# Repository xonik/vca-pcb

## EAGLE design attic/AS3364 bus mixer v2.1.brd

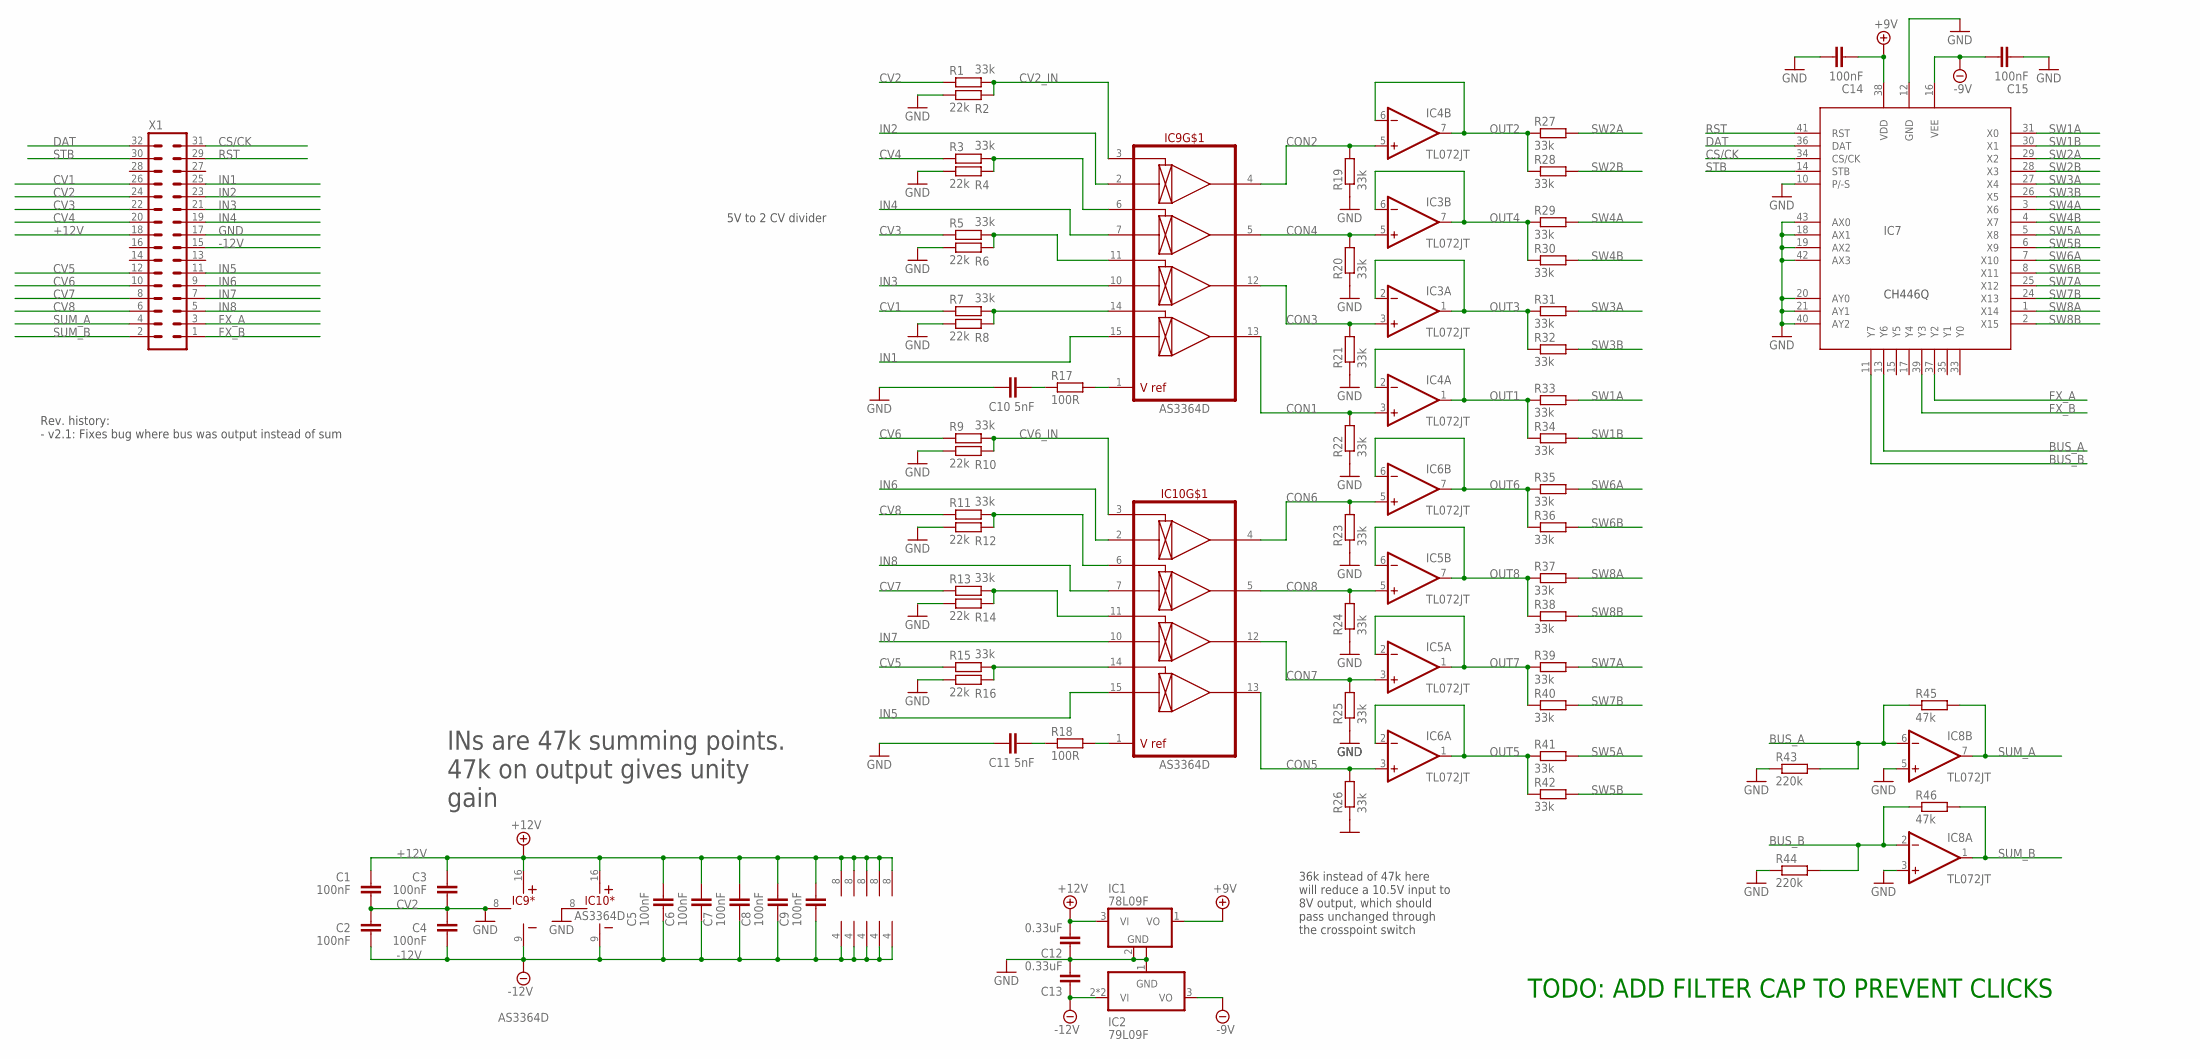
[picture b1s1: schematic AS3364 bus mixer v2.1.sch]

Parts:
C1, C2, C3, C4, C5, C6, C7, C8, C9, C14, C15: 100nF; C0402
C10, C11: 5nF; C0402
C12, C13: 0.33uF; C0603
IC1: 78L09F; SOT89
IC2: 79L09F; SOT89
IC3, IC4, IC5, IC6, IC8: TL072JT; TSSOP8J
IC7: CH446Q; LQFP-44-J
IC9, IC10: AS3364D; DIL16J
R1, R3, R5, R7, R9, R11, R13, R15, R19, R20, R21, R22, R23, R24, R25, R26, R27, R28, R29, R30, R31, R32, R33, R34, R35, R36, R37, R38, R39, R40, R41, R42: 33k; R0402
R2, R4, R6, R8, R10, R12, R14, R16: 22k; R0402
R17, R18: 100R; R0402
R43, R44: 220k; R0402
R45, R46: 47k; R0402
X1: MA16-2WJ

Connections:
+9V: C14.1, IC1.1 (VO), IC7.38 (VDD)
+12V: C1.2, C3.2, C5.2, C6.2, C7.2, C8.2, C9.2, C12.2, IC1.3 (VI), IC3.8 (V+), IC4.8 (V+), IC5.8 (V+), IC6.8 (V+), IC8.8 (V+), IC9.16 (V+), IC10.16 (V+), X1.18
-9V: C15.2, IC2.3 (VO), IC7.16 (VEE)
-12V: C2.1, C4.1, C5.1, C6.1, C7.1, C8.1, C9.1, C13.1, IC2.2 (VI), IC2.2@1 (VI), IC3.4 (V-), IC4.4 (V-), IC5.4 (V-), IC6.4 (V-), IC8.4 (V-), IC9.9 (V-), IC10.9 (V-), X1.15
BUS_A: IC7.13 (Y6), IC8.6 (-IN), R43.2, R45.1
BUS_B: IC7.11 (Y7), IC8.2 (-IN), R44.2, R46.1
CON1: IC4.3 (+IN), IC9.13 (OUT4), R22.2
CON2: IC4.5 (+IN), IC9.4 (OUT1), R19.2
CON3: IC3.3 (+IN), IC9.12 (OUT3), R21.2
CON4: IC3.5 (+IN), IC9.5 (OUT2), R20.2
CON5: IC6.3 (+IN), IC10.13 (OUT4), R26.2
CON6: IC6.5 (+IN), IC10.4 (OUT1), R23.2
CON7: IC5.3 (+IN), IC10.12 (OUT3), R25.2
CON8: IC5.5 (+IN), IC10.5 (OUT2), R24.2
CS/CK: IC7.34 (CS/CK), X1.31
CV1: R7.1, X1.26
CV2: R1.1, X1.24
CV2_IN: IC9.3 (CV1), R1.2, R2.2
CV3: R5.1, X1.22
CV4: R3.1, X1.20
CV5: R15.1, X1.12
CV6: R9.1, X1.10
CV6_IN: IC10.3 (CV1), R9.2, R10.2
CV7: R13.1, X1.8
CV8: R11.1, X1.6
DAT: IC7.36 (DAT), X1.32
FX_A: IC7.37 (Y2), X1.3
FX_B: IC7.39 (Y3), X1.1
GND: C1.1, C2.2, C3.1, C4.2, C10.1, C11.1, C12.1, C13.2, C14.2, C15.1, IC1.2 (GND), IC1.2@1 (GND), IC2.1 (GND), IC7.10 (P/-S), IC7.12 (GND), IC7.18 (AX1), IC7.19 (AX2), IC7.20 (AY0), IC7.21 (AY1), IC7.40 (AY2), IC7.42 (AX3), IC7.43 (AX0), IC8.3 (+IN), IC8.5 (+IN), IC9.8 (GND), IC10.8 (GND), R2.1, R4.1, R6.1, R8.1, R10.1, R12.1, R14.1, R16.1, R19.1, R20.1, R21.1, R22.1, R23.1, R24.1, R25.1, R26.1, R43.1, R44.1, X1.17
IN1: IC9.15 (IN4), X1.25
IN2: IC9.2 (IN1), X1.23
IN3: IC9.10 (IN3), X1.21
IN4: IC9.7 (IN2), X1.19
IN5: IC10.15 (IN4), X1.11
IN6: IC10.2 (IN1), X1.9
IN7: IC10.10 (IN3), X1.7
IN8: IC10.7 (IN2), X1.5
unnamed: IC10.1 (VREF), R18.2
unnamed: IC9.1 (VREF), R17.2
unnamed: IC10.6 (CV2), R11.2, R12.2
unnamed: IC10.11 (CV3), R13.2, R14.2
unnamed: IC10.14 (CV4), R15.2, R16.2
unnamed: C11.2, R18.1
unnamed: IC9.6 (CV2), R3.2, R4.2
unnamed: IC9.11 (CV3), R5.2, R6.2
unnamed: C10.2, R17.1
unnamed: IC9.14 (CV4), R7.2, R8.2
OUT1: IC4.1 (OUT), IC4.2 (-IN), R33.1, R34.1
OUT2: IC4.6 (-IN), IC4.7 (OUT), R27.1, R28.1
OUT3: IC3.1 (OUT), IC3.2 (-IN), R31.1, R32.1
OUT4: IC3.6 (-IN), IC3.7 (OUT), R29.1, R30.1
OUT5: IC6.1 (OUT), IC6.2 (-IN), R41.1, R42.1
OUT6: IC6.6 (-IN), IC6.7 (OUT), R35.1, R36.1
OUT7: IC5.1 (OUT), IC5.2 (-IN), R39.1, R40.1
OUT8: IC5.6 (-IN), IC5.7 (OUT), R37.1, R38.1
RST: IC7.41 (RST), X1.29
STB: IC7.14 (STB), X1.30
SUM_A: IC8.7 (OUT), R45.2, X1.4
SUM_B: IC8.1 (OUT), R46.2, X1.2
SW1A: IC7.31 (X0), R33.2
SW1B: IC7.30 (X1), R34.2
SW2A: IC7.29 (X2), R27.2
SW2B: IC7.28 (X3), R28.2
SW3A: IC7.27 (X4), R31.2
SW3B: IC7.26 (X5), R32.2
SW4A: IC7.3 (X6), R29.2
SW4B: IC7.4 (X7), R30.2
SW5A: IC7.5 (X8), R41.2
SW5B: IC7.6 (X9), R42.2
SW6A: IC7.7 (X10), R35.2
SW6B: IC7.8 (X11), R36.2
SW7A: IC7.25 (X12), R39.2
SW7B: IC7.24 (X13), R40.2
SW8A: IC7.1 (X14), R37.2
SW8B: IC7.2 (X15), R38.2

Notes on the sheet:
INs are 47k summing points. 47k on output gives unity gain
5V to 2 CV divider
36k instead of 47k here will reduce a 10.5V input to 8V output, which should pass unchanged through the crosspoint switch
Rev. history: - v2.1: Fixes bug where bus was output instead of sum
TODO: ADD FILTER CAP TO PREVENT CLICKS

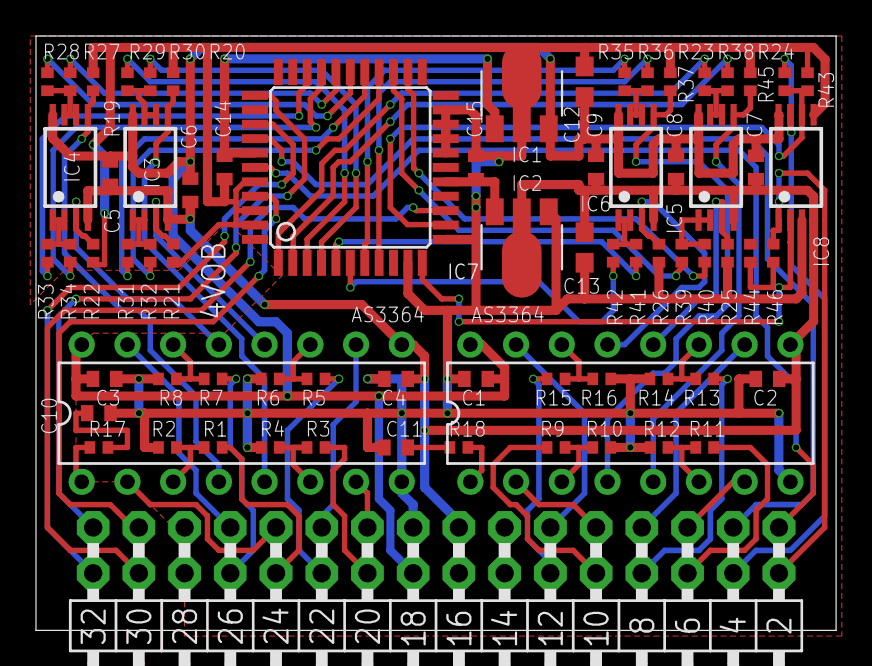
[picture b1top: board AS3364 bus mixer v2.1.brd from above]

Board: 2 copper layers, 44.5 x 33.0 mm, 73 parts (1 on the bottom side), 75 nets.

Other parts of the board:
U$1: XONIK_LOGO_28

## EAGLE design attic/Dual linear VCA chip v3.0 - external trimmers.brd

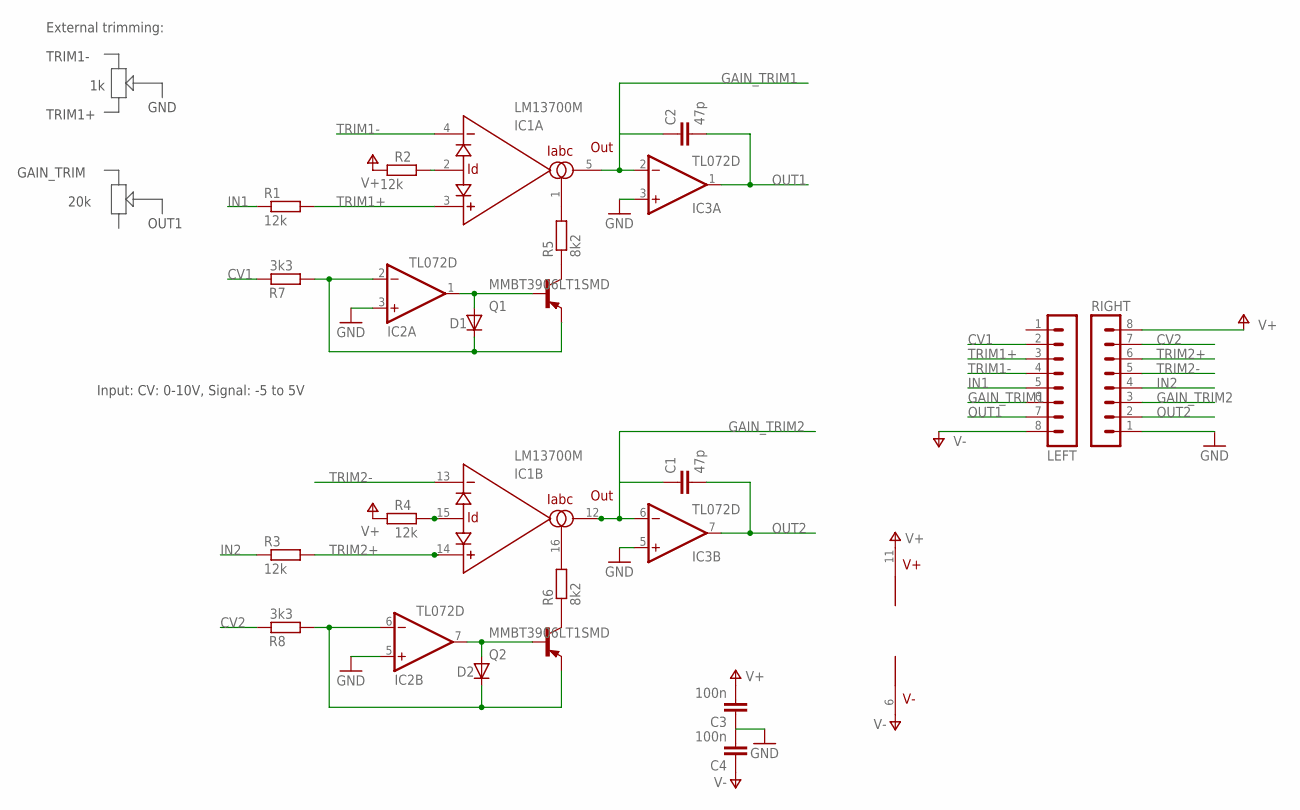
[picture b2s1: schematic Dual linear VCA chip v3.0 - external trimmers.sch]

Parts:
C1, C2: 47p; C0805
C3, C4: 100n; C0805
D1, D2: DIODE-SOD80C; SOD80C
IC1: LM13700M; SO16
IC2, IC3: TL072D; SO08
LEFT: MA08-1JC; MA08-1J
Q1, Q2: MMBT3906LT1SMD; SOT23-BEC
R1, R2, R3, R4: 12k; R0805
R5, R6: 8k2; R0805
R7, R8: 3k3; R0805
RIGHT: MA08-1JC; MA08-1J

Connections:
CV1: LEFT.2, R7.2
CV2: R8.2, RIGHT.7
GAIN_TRIM1: C2.1, IC1.5 (OUT), IC3.2 (-IN), LEFT.6
GAIN_TRIM2: C1.1, IC1.12 (OUT), IC3.6 (-IN), RIGHT.3
GND: C3.1, C4.2, IC2.3 (+IN), IC2.5 (+IN), IC3.3 (+IN), IC3.5 (+IN), RIGHT.1
IN1: LEFT.5, R1.1
IN2: R3.1, RIGHT.4
unnamed: Q1.C, R5.1
unnamed: Q2.C, R6.1
unnamed: D1.C, IC2.2 (-IN), Q1.E, R7.1
unnamed: IC1.1 (IABC), R5.2
unnamed: IC1.2 (ID), R2.2
unnamed: D2.A, IC2.7 (OUT), Q2.B
unnamed: D1.A, IC2.1 (OUT), Q1.B
unnamed: D2.C, IC2.6 (-IN), Q2.E, R8.1
unnamed: IC1.16 (IABC), R6.2
unnamed: IC1.15 (ID), R4.2
OUT1: C2.2, IC3.1 (OUT), LEFT.7
OUT2: C1.2, IC3.7 (OUT), RIGHT.2
TRIM1+: IC1.3 (+IN), LEFT.3, R1.2
TRIM1-: IC1.4 (-IN), LEFT.4
TRIM2+: IC1.14 (+IN), R3.2, RIGHT.6
TRIM2-: IC1.13 (-IN), RIGHT.5
V+: C3.2, IC1.11 (V+), IC2.8 (V+), IC3.8 (V+), R2.1, R4.1, RIGHT.8
V-: C4.1, IC1.6 (V-), IC2.4 (V-), IC3.4 (V-), LEFT.8

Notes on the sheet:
Input: CV: 0-10V, Signal: -5 to 5V
TRIM1-
TRIM1+
GND
External trimming:
GAIN_TRIM
OUT1
20k

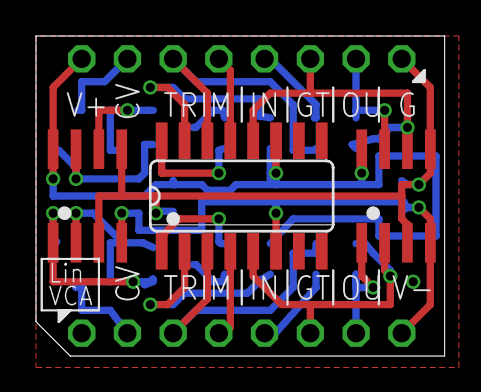
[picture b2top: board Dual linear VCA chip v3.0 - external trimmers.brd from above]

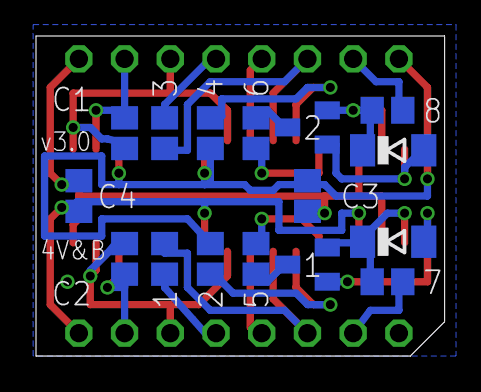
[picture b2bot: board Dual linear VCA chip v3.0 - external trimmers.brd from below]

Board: 2 copper layers, 22.7 x 17.8 mm, 21 parts (16 on the bottom side), 25 nets.

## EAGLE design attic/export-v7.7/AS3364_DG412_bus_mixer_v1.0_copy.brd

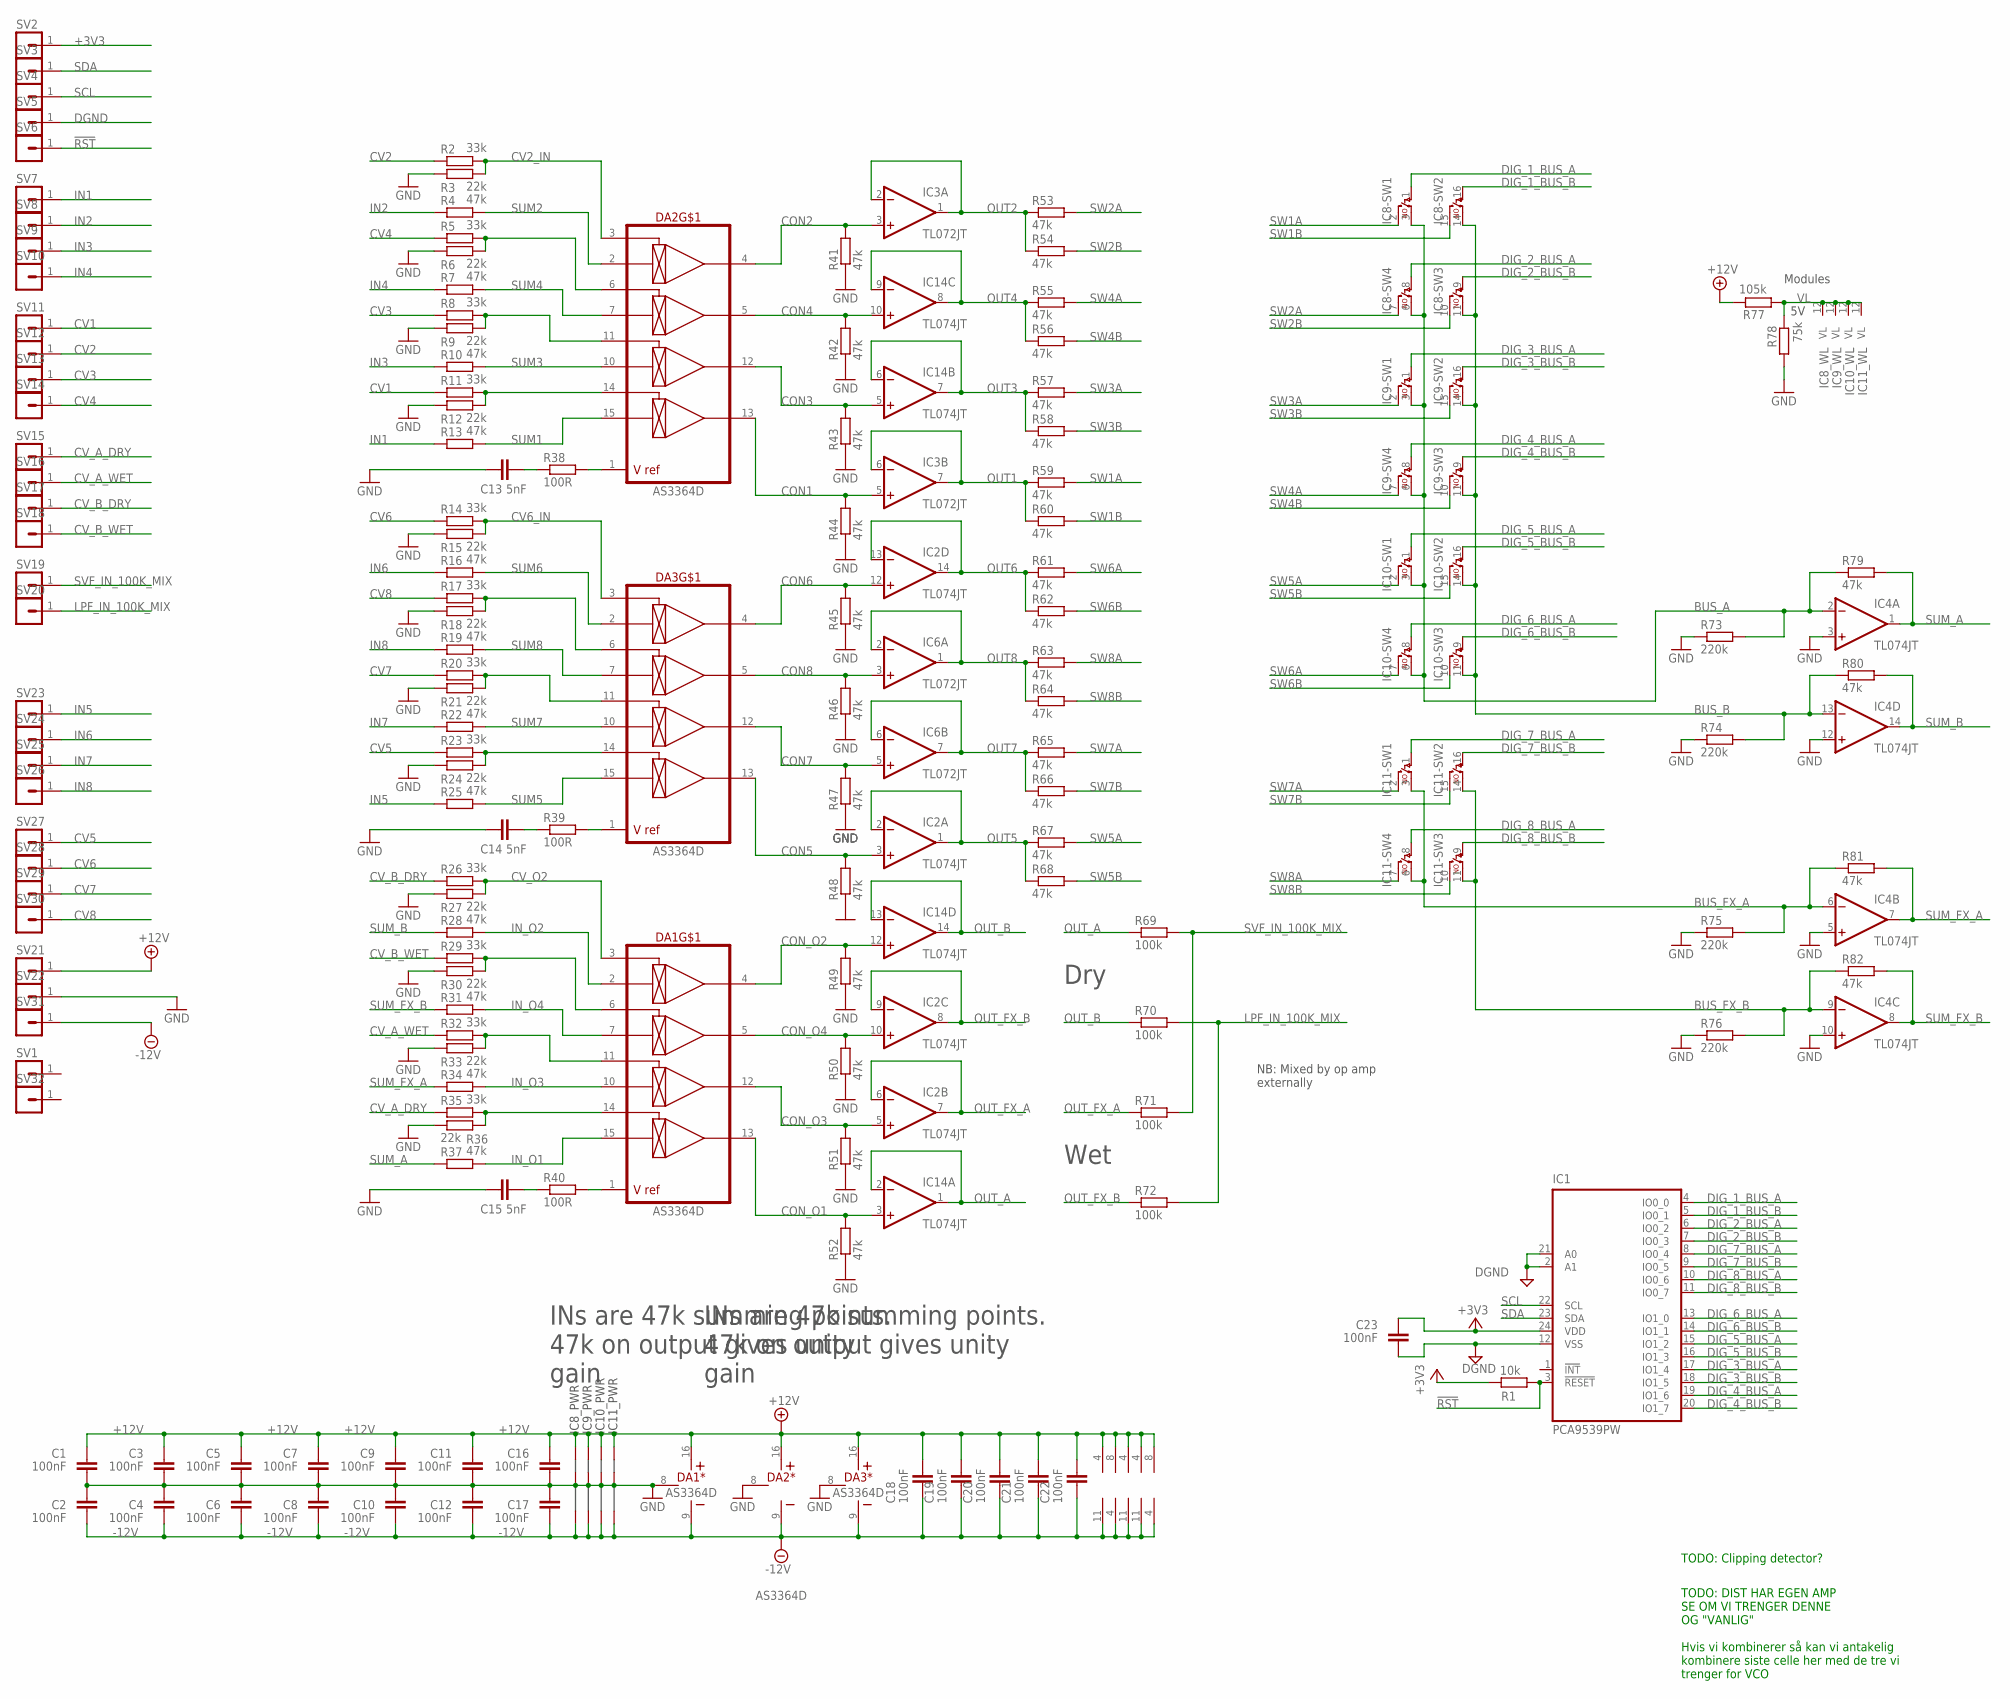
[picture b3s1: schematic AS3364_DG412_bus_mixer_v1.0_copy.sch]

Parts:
C1, C2, C3, C4, C5, C6, C7, C8, C9, C10, C11, C12, C16, C17, C18, C19, C20, C21, C22, C23: 100nF; C0402
C13, C14, C15: 5nF; C0402
DA1, DA2, DA3: AS3364D; DIL16J
IC1: PCA9539PW; TSSOP24J
IC2, IC4, IC14: TL074JT; TSSOP14J
IC3, IC6: TL072JT; TSSOP8J
IC8, IC9, IC10, IC11: DG412-J; DIL16J
R1: 10k; R0402
R2, R5, R8, R11, R14, R17, R20, R23, R26, R29, R32, R35: 33k; R0402
R3, R6, R9, R12, R15, R18, R21, R24, R27, R30, R33, R36: 22k; R0402
R4, R7, R10, R13, R16, R19, R22, R25, R28, R31, R34, R37, R41, R42, R43, R44, R45, R46, R47, R48, R49, R50, R51, R52, R53, R54, R55, R56, R57, R58, R59, R60, R61, R62, R63, R64, R65, R66, R67, R68, R79, R80, R81, R82: 47k; R0402
R38, R39, R40: 100R; R0402
R69, R70, R71, R72: 100k; R0402
R73, R74, R75, R76: 220k; R0402
R77: 105k; R0402
R78: 75k; R0402
SV1, SV2, SV3, SV4, SV5, SV6, SV7, SV8, SV9, SV10, SV11, SV12, SV13, SV14, SV15, SV16, SV17, SV18, SV19, SV20, SV21, SV22, SV23, SV24, SV25, SV26, SV27, SV28, SV29, SV30, SV31, SV32: MA01-1JP; SIP-PIN01-1J

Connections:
!RST: IC1.3 (!RESET), R1.2, SV6.1
+3V3: C23.2, IC1.24 (VDD), R1.1, SV2.1
+12V: C1.2, C3.2, C5.2, C7.2, C9.2, C11.2, C16.2, C18.2, C19.2, C20.2, C21.2, C22.2, DA1.16 (V+), DA2.16 (V+), DA3.16 (V+), IC2.4 (V+), IC3.8 (V+), IC4.4 (V+), IC6.8 (V+), IC8.13 (+15V), IC9.13 (+15V), IC10.13 (+15V), IC11.13 (+15V), IC14.4 (V+), R77.1, SV21.1
-12V: C2.1, C4.1, C6.1, C8.1, C10.1, C12.1, C17.1, C18.1, C19.1, C20.1, C21.1, C22.1, DA1.9 (V-), DA2.9 (V-), DA3.9 (V-), IC2.11 (V-), IC3.4 (V-), IC4.11 (V-), IC6.4 (V-), IC8.4 (-15V), IC9.4 (-15V), IC10.4 (-15V), IC11.4 (-15V), IC14.11 (V-), SV31.1
BUS_A: IC4.2 (-IN), IC8.3 (S), IC8.6 (S), IC9.3 (S), IC9.6 (S), IC10.3 (S), IC10.6 (S), R73.2, R79.1
BUS_B: IC4.13 (-IN), IC8.11 (S), IC8.14 (S), IC9.11 (S), IC9.14 (S), IC10.11 (S), IC10.14 (S), R74.2, R80.1
BUS_FX_A: IC4.6 (-IN), IC11.3 (S), IC11.6 (S), R75.2, R81.1
BUS_FX_B: IC4.9 (-IN), IC11.11 (S), IC11.14 (S), R76.2, R82.1
CON1: DA2.13 (OUT4), IC3.5 (+IN), R44.2
CON2: DA2.4 (OUT1), IC3.3 (+IN), R41.2
CON3: DA2.12 (OUT3), IC14.5 (+IN), R43.2
CON4: DA2.5 (OUT2), IC14.10 (+IN), R42.2
CON5: DA3.13 (OUT4), IC2.3 (+IN), R48.2
CON6: DA3.4 (OUT1), IC2.12 (+IN), R45.2
CON7: DA3.12 (OUT3), IC6.5 (+IN), R47.2
CON8: DA3.5 (OUT2), IC6.3 (+IN), R46.2
CON_O1: DA1.13 (OUT4), IC14.3 (+IN), R52.2
CON_O2: DA1.4 (OUT1), IC14.12 (+IN), R49.2
CON_O3: DA1.12 (OUT3), IC2.5 (+IN), R51.2
CON_O4: DA1.5 (OUT2), IC2.10 (+IN), R50.2
CV1: R11.1, SV11.1
CV2: R2.1, SV12.1
CV2_IN: DA2.3 (CV1), R2.2, R3.2
CV3: R8.1, SV13.1
CV4: R5.1, SV14.1
CV5: R23.1, SV27.1
CV6: R14.1, SV28.1
CV6_IN: DA3.3 (CV1), R14.2, R15.2
CV7: R20.1, SV29.1
CV8: R17.1, SV30.1
CV_A_DRY: R35.1, SV15.1
CV_A_WET: R32.1, SV16.1
CV_B_DRY: R26.1, SV17.1
CV_B_WET: R29.1, SV18.1
CV_O2: DA1.3 (CV1), R26.2, R27.2
DGND: C23.1, IC1.2 (A1), IC1.12 (VSS), IC1.21 (A0), SV5.1
DIG_1_BUS_A: IC1.4 (IO0_0), IC8.1 (C)
DIG_1_BUS_B: IC1.5 (IO0_1), IC8.16 (C)
DIG_2_BUS_A: IC1.6 (IO0_2), IC8.8 (C)
DIG_2_BUS_B: IC1.7 (IO0_3), IC8.9 (C)
DIG_3_BUS_A: IC1.17 (IO1_4), IC9.1 (C)
DIG_3_BUS_B: IC1.18 (IO1_5), IC9.16 (C)
DIG_4_BUS_A: IC1.19 (IO1_6), IC9.8 (C)
DIG_4_BUS_B: IC1.20 (IO1_7), IC9.9 (C)
DIG_5_BUS_A: IC1.15 (IO1_2), IC10.1 (C)
DIG_5_BUS_B: IC1.16 (IO1_3), IC10.16 (C)
DIG_6_BUS_A: IC1.13 (IO1_0), IC10.8 (C)
DIG_6_BUS_B: IC1.14 (IO1_1), IC10.9 (C)
DIG_7_BUS_A: IC1.8 (IO0_4), IC11.1 (C)
DIG_7_BUS_B: IC1.9 (IO0_5), IC11.16 (C)
DIG_8_BUS_A: IC1.10 (IO0_6), IC11.8 (C)
DIG_8_BUS_B: IC1.11 (IO0_7), IC11.9 (C)
GND: C1.1, C2.2, C3.1, C4.2, C5.1, C6.2, C7.1, C8.2, C9.1, C10.2, C11.1, C12.2, C13.1, C14.1, C15.1, C16.1, C17.2, DA1.8 (GND), DA2.8 (GND), DA3.8 (GND), IC4.3 (+IN), IC4.5 (+IN), IC4.10 (+IN), IC4.12 (+IN), IC8.5 (AGND), IC9.5 (AGND), IC10.5 (AGND), IC11.5 (AGND), R3.1, R6.1, R9.1, R12.1, R15.1, R18.1, R21.1, R24.1, R27.1, R30.1, R33.1, R36.1, R41.1, R42.1, R43.1, R44.1, R45.1, R46.1, R47.1, R48.1, R49.1, R50.1, R51.1, R52.1, R73.1, R74.1, R75.1, R76.1, R78.2, SV22.1
IN1: R13.1, SV7.1
IN2: R4.1, SV8.1
IN3: R10.1, SV9.1
IN4: R7.1, SV10.1
IN5: R25.1, SV23.1
IN6: R16.1, SV24.1
IN7: R22.1, SV25.1
IN8: R19.1, SV26.1
IN_O1: DA1.15 (IN4), R37.2
IN_O2: DA1.2 (IN1), R28.2
IN_O3: DA1.10 (IN3), R34.2
IN_O4: DA1.7 (IN2), R31.2
LPF_IN_100K_MIX: R70.2, R72.2, SV20.1
unnamed: DA3.1 (VREF), R39.2
unnamed: DA2.1 (VREF), R38.2
unnamed: DA3.6 (CV2), R17.2, R18.2
unnamed: DA3.11 (CV3), R20.2, R21.2
unnamed: DA3.14 (CV4), R23.2, R24.2
unnamed: C14.2, R39.1
unnamed: DA1.1 (VREF), R40.2
unnamed: DA2.6 (CV2), R5.2, R6.2
unnamed: DA1.6 (CV2), R29.2, R30.2
unnamed: DA2.11 (CV3), R8.2, R9.2
unnamed: DA1.11 (CV3), R32.2, R33.2
unnamed: C13.2, R38.1
unnamed: DA1.14 (CV4), R35.2, R36.2
unnamed: C15.2, R40.1
unnamed: DA2.14 (CV4), R11.2, R12.2
OUT1: IC3.6 (-IN), IC3.7 (OUT), R59.1, R60.1
OUT2: IC3.1 (OUT), IC3.2 (-IN), R53.1, R54.1
OUT3: IC14.6 (-IN), IC14.7 (OUT), R57.1, R58.1
OUT4: IC14.8 (OUT), IC14.9 (-IN), R55.1, R56.1
OUT5: IC2.1 (OUT), IC2.2 (-IN), R67.1, R68.1
OUT6: IC2.13 (-IN), IC2.14 (OUT), R61.1, R62.1
OUT7: IC6.6 (-IN), IC6.7 (OUT), R65.1, R66.1
OUT8: IC6.1 (OUT), IC6.2 (-IN), R63.1, R64.1
OUT_A: IC14.1 (OUT), IC14.2 (-IN), R69.1
OUT_B: IC14.13 (-IN), IC14.14 (OUT), R70.1
OUT_FX_A: IC2.6 (-IN), IC2.7 (OUT), R71.1
OUT_FX_B: IC2.8 (OUT), IC2.9 (-IN), R72.1
SCL: IC1.22 (SCL), SV4.1
SDA: IC1.23 (SDA), SV3.1
SUM1: DA2.15 (IN4), R13.2
SUM2: DA2.2 (IN1), R4.2
SUM3: DA2.10 (IN3), R10.2
SUM4: DA2.7 (IN2), R7.2
SUM5: DA3.15 (IN4), R25.2
SUM6: DA3.2 (IN1), R16.2
SUM7: DA3.10 (IN3), R22.2
SUM8: DA3.7 (IN2), R19.2
SUM_A: IC4.1 (OUT), R37.1, R79.2
SUM_B: IC4.14 (OUT), R28.1, R80.2
SUM_FX_A: IC4.7 (OUT), R34.1, R81.2
SUM_FX_B: IC4.8 (OUT), R31.1, R82.2
SVF_IN_100K_MIX: R69.2, R71.2, SV19.1
SW1A: IC8.2 (D), R59.2
SW1B: IC8.15 (D), R60.2
SW2A: IC8.7 (D), R53.2
SW2B: IC8.10 (D), R54.2
SW3A: IC9.2 (D), R57.2
SW3B: IC9.15 (D), R58.2
SW4A: IC9.7 (D), R55.2
SW4B: IC9.10 (D), R56.2
SW5A: IC10.2 (D), R67.2
SW5B: IC10.15 (D), R68.2
SW6A: IC10.7 (D), R61.2
SW6B: IC10.10 (D), R62.2
SW7A: IC11.2 (D), R65.2
SW7B: IC11.15 (D), R66.2
SW8A: IC11.7 (D), R63.2
SW8B: IC11.10 (D), R64.2
VL: IC8.12 (VL), IC9.12 (VL), IC10.12 (VL), IC11.12 (VL), R77.2, R78.1

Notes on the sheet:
INs are 47k summing points. 47k on output gives unity gain
TODO: DIST HAR EGEN AMP SE OM VI TRENGER DENNE OG "VANLIG" Hvis vi kombinerer så kan vi antakelig kombinere siste celle her med de tre vi trenger for VCO
TODO: Clipping detector?
Dry
Wet
NB: Mixed by op amp externally
Modules

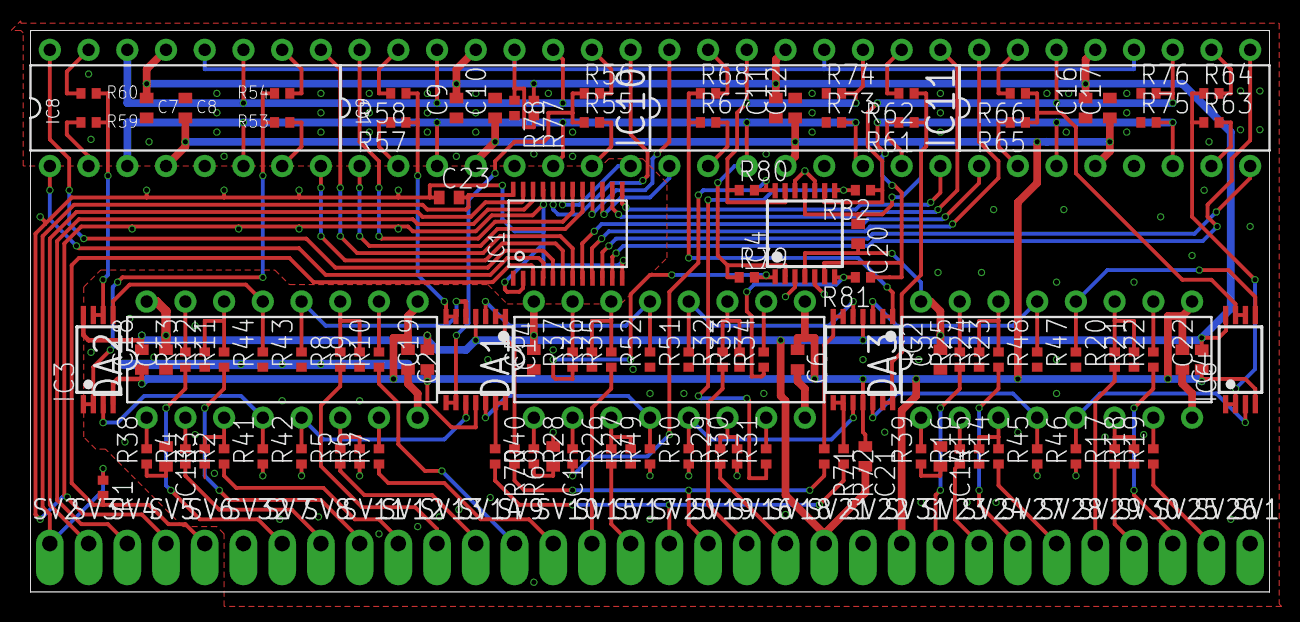
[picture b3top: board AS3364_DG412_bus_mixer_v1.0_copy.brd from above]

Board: 2 copper layers, 81.3 x 36.8 mm, 150 parts (0 on the bottom side), 125 nets.

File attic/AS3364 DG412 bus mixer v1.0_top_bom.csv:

Comment,Designator,Footprint,LCSC Part #
5nF,C13 C14 C15,R0402,C1538
10k,R1,R0402,C25744
22k,R3 R6 R9 R12 R15 R18 R21 R24 R27 R30 R33 R36,R0402,C25768
33k,R2 R5 R8 R11 R14 R17 R20 R23 R26 R29 R32 R35,R0402,C25779
33pF,C24 C25 C26 C27,R0402,C1562
47k,R4 R7 R10 R13 R16 R19 R22 R25 R28 R31 R34 R37 R41 R42 R43 R44 R45 R46 R47 R48 R49 R50 R51 R52 R53 R54 R55 R56 R57 R58 R59 R60 R61 R62 R63 R64 R65 R66 R67 R68 R79 R80 R81 R82,R0402,C25792
75k,R78,R0402,C3016015
100R,R38 R39 R40,R0402,C25076
100k,R69 R70 R71 R72,R0402,C25741
100nF,C1 C2 C3 C4 C5 C6 C7 C8 C9 C10 C11 C12 C16 C17 C18 C19 C20 C21 C22 C23,C0402,C307331
105k,R77,R0402,C102762
220k,R73 R74 R75 R76,R0402,C25767
AS3364D,DA1 DA2 DA3,DIL16J,C72130
DG412-J,IC8 IC9 IC10 IC11,DIL16J,C72130
PCA9539PW,IC1,TSSOP24J,C2687996
TL072JT,IC3 IC6,TSSOP8J,C85346
TL074JT,IC2 IC4 IC14,TSSOP14J,C2652279
CON8,SV1 SV3 SV4 SV33,CON8,C706871

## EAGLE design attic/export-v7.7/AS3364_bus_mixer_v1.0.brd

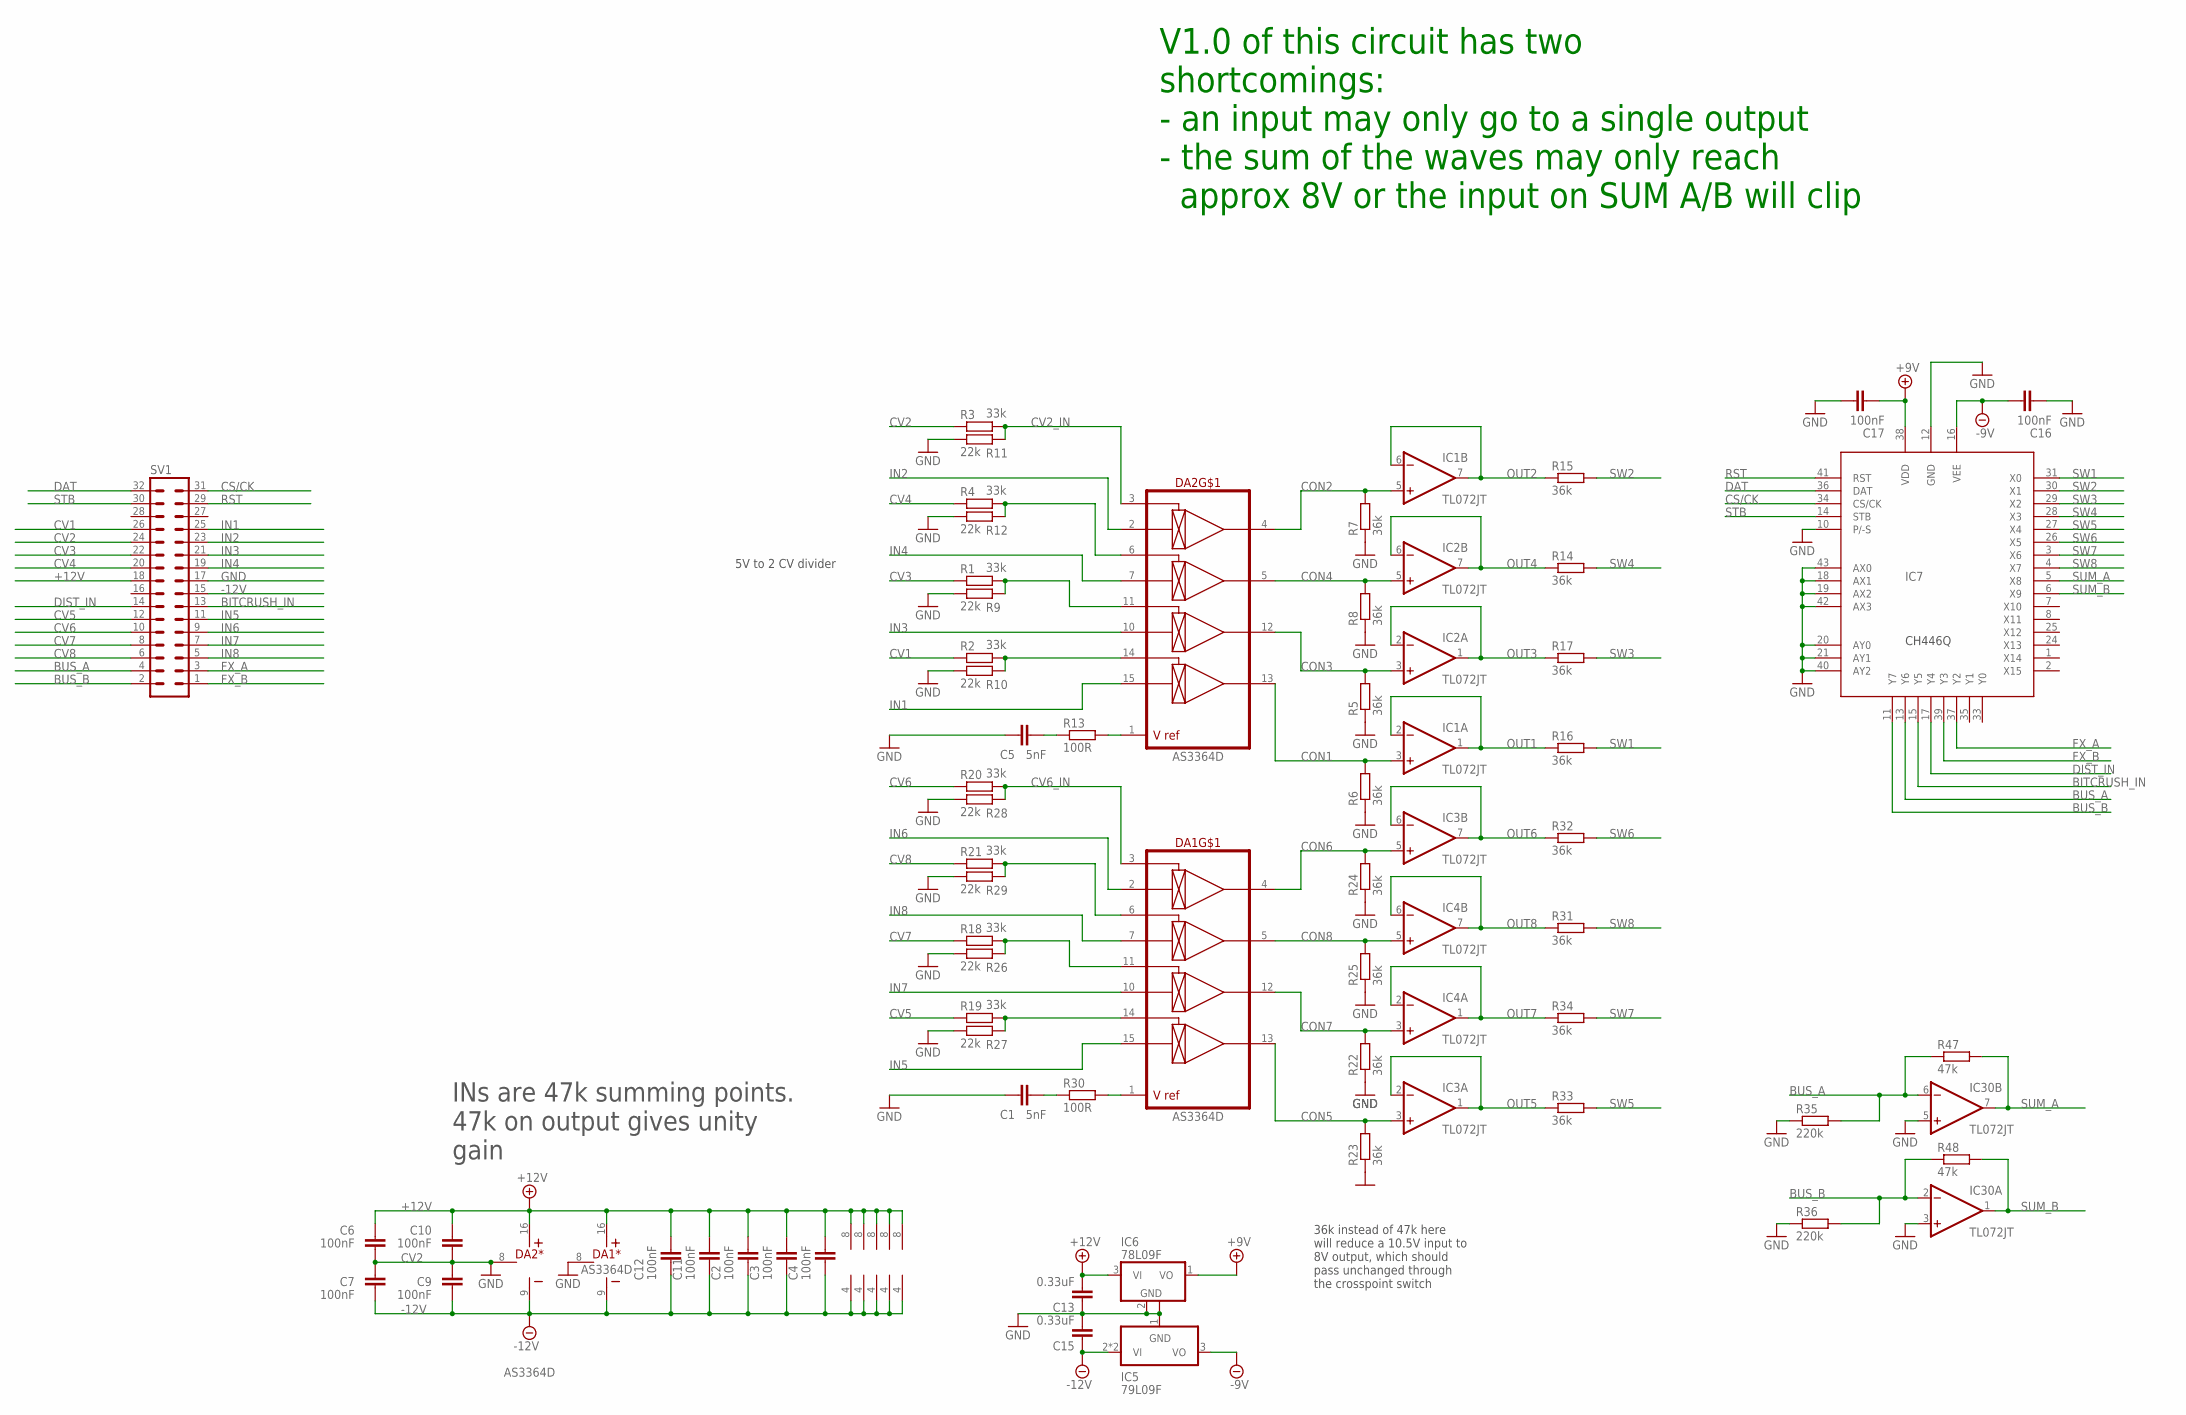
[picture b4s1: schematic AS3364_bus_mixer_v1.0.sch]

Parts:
C1, C5: 5nF; C0402
C2, C3, C4, C6, C7, C9, C10, C11, C12, C16, C17: 100nF; C0402
C13, C15: 0.33uF; C0603
DA1, DA2: AS3364D; DIL16J
IC1, IC2, IC3, IC4, IC30: TL072JT; TSSOP8J
IC5: 79L09F; SOT89
IC6: 78L09F; SOT89
IC7: CH446Q; LQFP-44-J
R1, R2, R3, R4, R18, R19, R20, R21: 33k; R0402
R5, R6, R7, R8, R14, R15, R16, R17, R22, R23, R24, R25, R31, R32, R33, R34: 36k; R0402
R9, R10, R11, R12, R26, R27, R28, R29: 22k; R0402
R13, R30: 100R; R0402
R35, R36: 220k; R0402
R47, R48: 47k; R0402
SV1: MA16-2WJ

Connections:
+9V: C17.1, IC6.1 (VO), IC7.38 (VDD)
+12V: C2.2, C3.2, C4.2, C6.2, C10.2, C11.2, C12.2, C13.2, DA1.16 (V+), DA2.16 (V+), IC1.8 (V+), IC2.8 (V+), IC3.8 (V+), IC4.8 (V+), IC6.3 (VI), IC30.8 (V+), SV1.18
-9V: C16.2, IC5.3 (VO), IC7.16 (VEE)
-12V: C2.1, C3.1, C4.1, C7.1, C9.1, C11.1, C12.1, C15.1, DA1.9 (V-), DA2.9 (V-), IC1.4 (V-), IC2.4 (V-), IC3.4 (V-), IC4.4 (V-), IC5.2 (VI), IC5.2@1 (VI), IC30.4 (V-), SV1.15
BITCRUSH_IN: IC7.15 (Y5), SV1.13
BUS_A: IC7.13 (Y6), IC30.6 (-IN), R35.2, R47.1, SV1.4
BUS_B: IC7.11 (Y7), IC30.2 (-IN), R36.2, R48.1, SV1.2
CON1: DA2.13 (OUT4), IC1.3 (+IN), R6.2
CON2: DA2.4 (OUT1), IC1.5 (+IN), R7.2
CON3: DA2.12 (OUT3), IC2.3 (+IN), R5.2
CON4: DA2.5 (OUT2), IC2.5 (+IN), R8.2
CON5: DA1.13 (OUT4), IC3.3 (+IN), R23.2
CON6: DA1.4 (OUT1), IC3.5 (+IN), R24.2
CON7: DA1.12 (OUT3), IC4.3 (+IN), R22.2
CON8: DA1.5 (OUT2), IC4.5 (+IN), R25.2
CS/CK: IC7.34 (CS/CK), SV1.31
CV1: R2.1, SV1.26
CV2: R3.1, SV1.24
CV2_IN: DA2.3 (CV1), R3.2, R11.2
CV3: R1.1, SV1.22
CV4: R4.1, SV1.20
CV5: R19.1, SV1.12
CV6: R20.1, SV1.10
CV6_IN: DA1.3 (CV1), R20.2, R28.2
CV7: R18.1, SV1.8
CV8: R21.1, SV1.6
DAT: IC7.36 (DAT), SV1.32
DIST_IN: IC7.17 (Y4), SV1.14
FX_A: IC7.37 (Y2), SV1.3
FX_B: IC7.39 (Y3), SV1.1
GND: C1.1, C5.1, C6.1, C7.2, C9.2, C10.1, C13.1, C15.2, C16.1, C17.2, DA1.8 (GND), DA2.8 (GND), IC5.1 (GND), IC6.2 (GND), IC6.2@1 (GND), IC7.10 (P/-S), IC7.12 (GND), IC7.18 (AX1), IC7.19 (AX2), IC7.20 (AY0), IC7.21 (AY1), IC7.40 (AY2), IC7.42 (AX3), IC7.43 (AX0), IC30.3 (+IN), IC30.5 (+IN), R5.1, R6.1, R7.1, R8.1, R9.1, R10.1, R11.1, R12.1, R22.1, R23.1, R24.1, R25.1, R26.1, R27.1, R28.1, R29.1, R35.1, R36.1, SV1.17
IN1: DA2.15 (IN4), SV1.25
IN2: DA2.2 (IN1), SV1.23
IN3: DA2.10 (IN3), SV1.21
IN4: DA2.7 (IN2), SV1.19
IN5: DA1.15 (IN4), SV1.11
IN6: DA1.2 (IN1), SV1.9
IN7: DA1.10 (IN3), SV1.7
IN8: DA1.7 (IN2), SV1.5
unnamed: DA1.1 (VREF), R30.2
unnamed: DA2.1 (VREF), R13.2
unnamed: DA1.6 (CV2), R21.2, R29.2
unnamed: DA1.11 (CV3), R18.2, R26.2
unnamed: DA1.14 (CV4), R19.2, R27.2
unnamed: C1.2, R30.1
unnamed: DA2.6 (CV2), R4.2, R12.2
unnamed: DA2.11 (CV3), R1.2, R9.2
unnamed: C5.2, R13.1
unnamed: DA2.14 (CV4), R2.2, R10.2
OUT1: IC1.1 (OUT), IC1.2 (-IN), R16.1
OUT2: IC1.6 (-IN), IC1.7 (OUT), R15.1
OUT3: IC2.1 (OUT), IC2.2 (-IN), R17.1
OUT4: IC2.6 (-IN), IC2.7 (OUT), R14.1
OUT5: IC3.1 (OUT), IC3.2 (-IN), R33.1
OUT6: IC3.6 (-IN), IC3.7 (OUT), R32.1
OUT7: IC4.1 (OUT), IC4.2 (-IN), R34.1
OUT8: IC4.6 (-IN), IC4.7 (OUT), R31.1
RST: IC7.41 (RST), SV1.29
STB: IC7.14 (STB), SV1.30
SUM_A: IC7.5 (X8), IC30.7 (OUT), R47.2
SUM_B: IC7.6 (X9), IC30.1 (OUT), R48.2
SW1: IC7.31 (X0), R16.2
SW2: IC7.30 (X1), R15.2
SW3: IC7.29 (X2), R17.2
SW4: IC7.28 (X3), R14.2
SW5: IC7.27 (X4), R33.2
SW6: IC7.26 (X5), R32.2
SW7: IC7.3 (X6), R34.2
SW8: IC7.4 (X7), R31.2

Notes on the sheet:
INs are 47k summing points. 47k on output gives unity gain
5V to 2 CV divider
36k instead of 47k here will reduce a 10.5V input to 8V output, which should pass unchanged through the crosspoint switch
V1.0 of this circuit has two shortcomings: - an input may only go to a single output - the sum of the waves may only reach approx 8V or the input on SUM A/B will clip

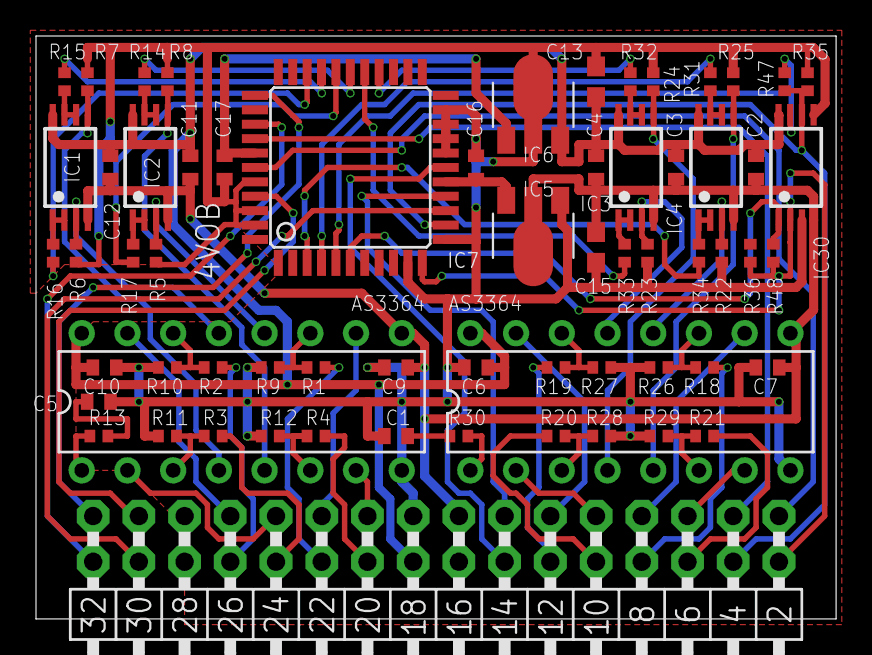
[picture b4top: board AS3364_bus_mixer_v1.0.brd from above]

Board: 2 copper layers, 44.5 x 32.4 mm, 65 parts (1 on the bottom side), 69 nets.

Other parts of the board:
U$1: XONIK_LOGO_28
